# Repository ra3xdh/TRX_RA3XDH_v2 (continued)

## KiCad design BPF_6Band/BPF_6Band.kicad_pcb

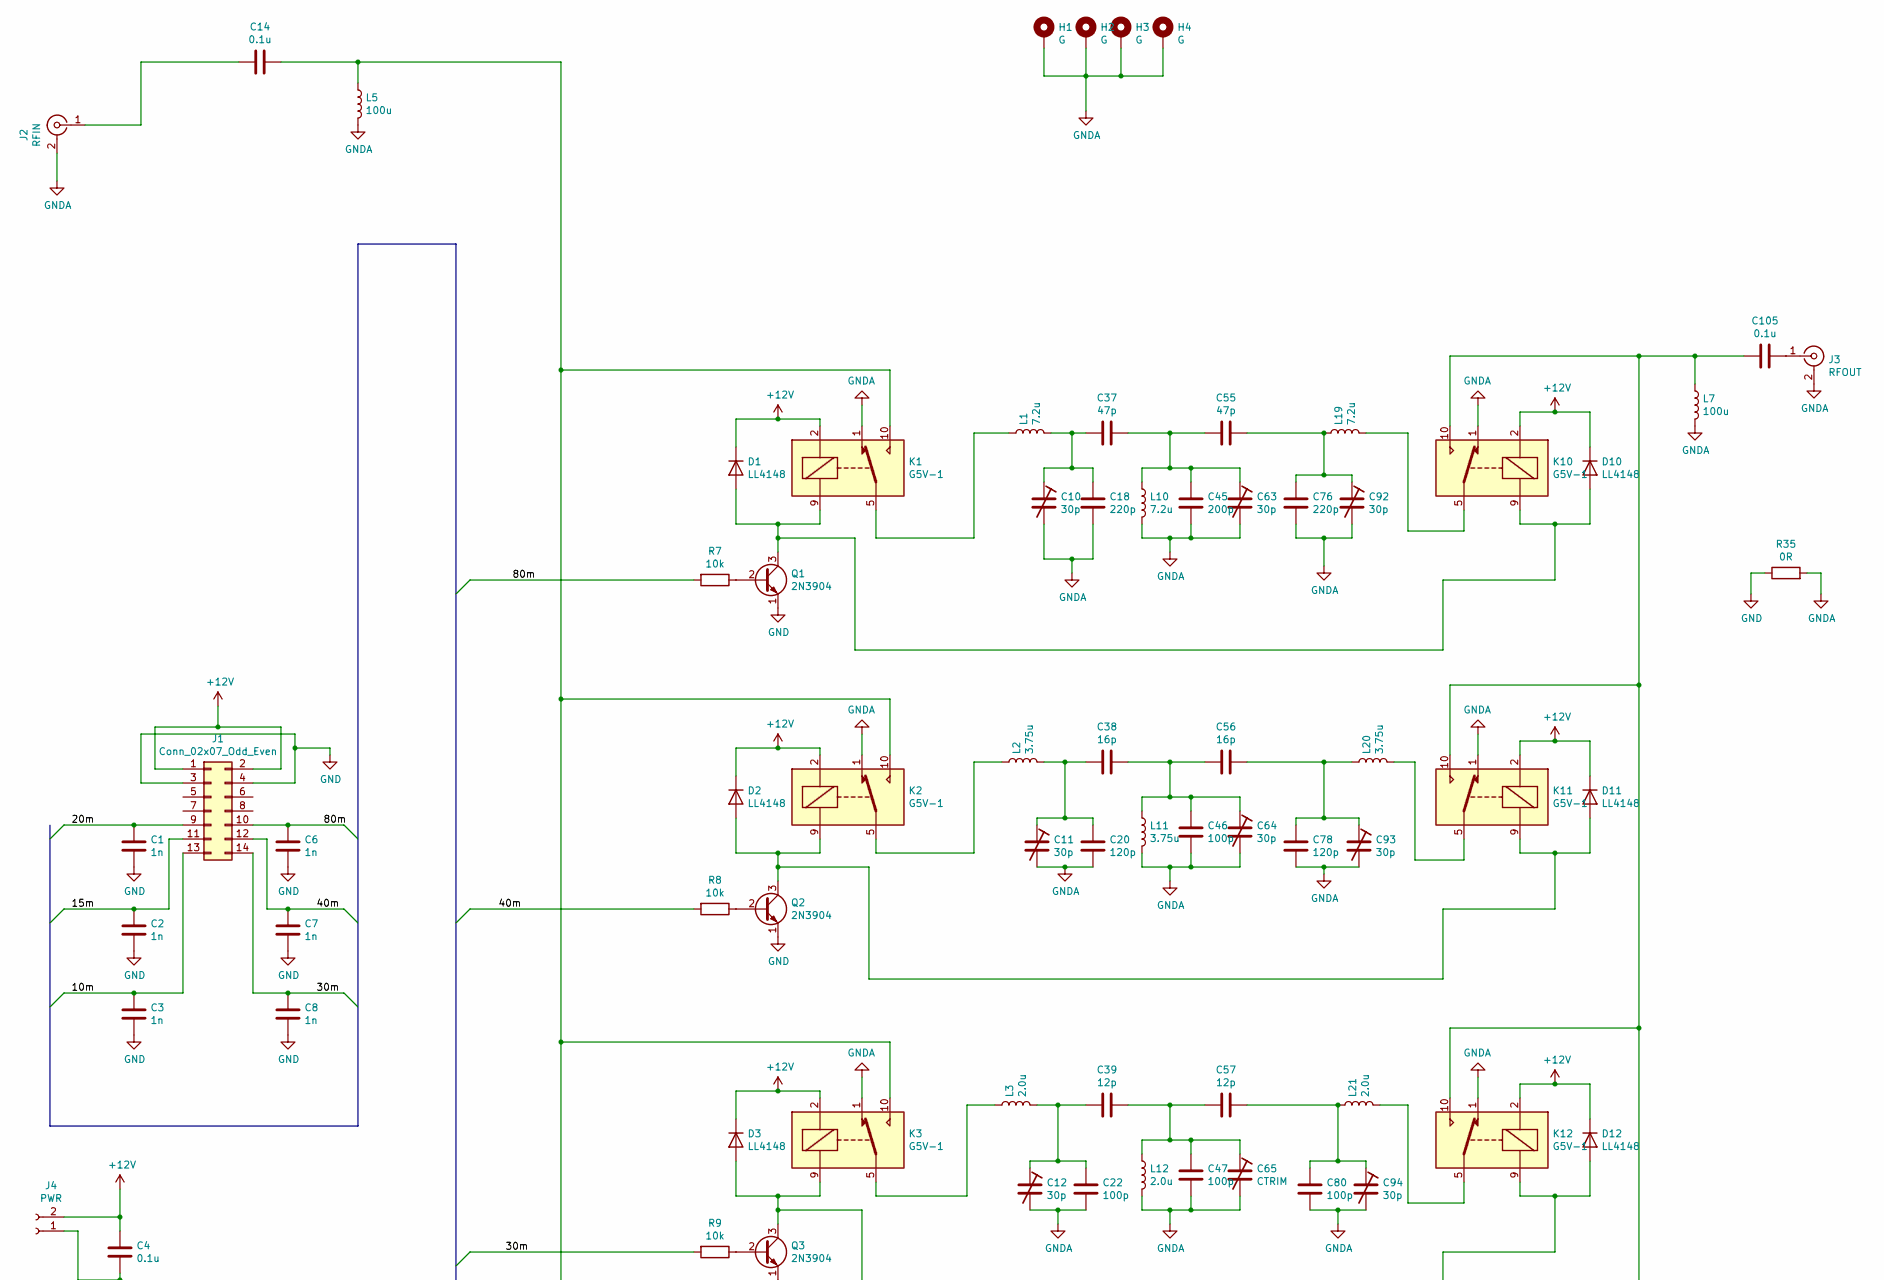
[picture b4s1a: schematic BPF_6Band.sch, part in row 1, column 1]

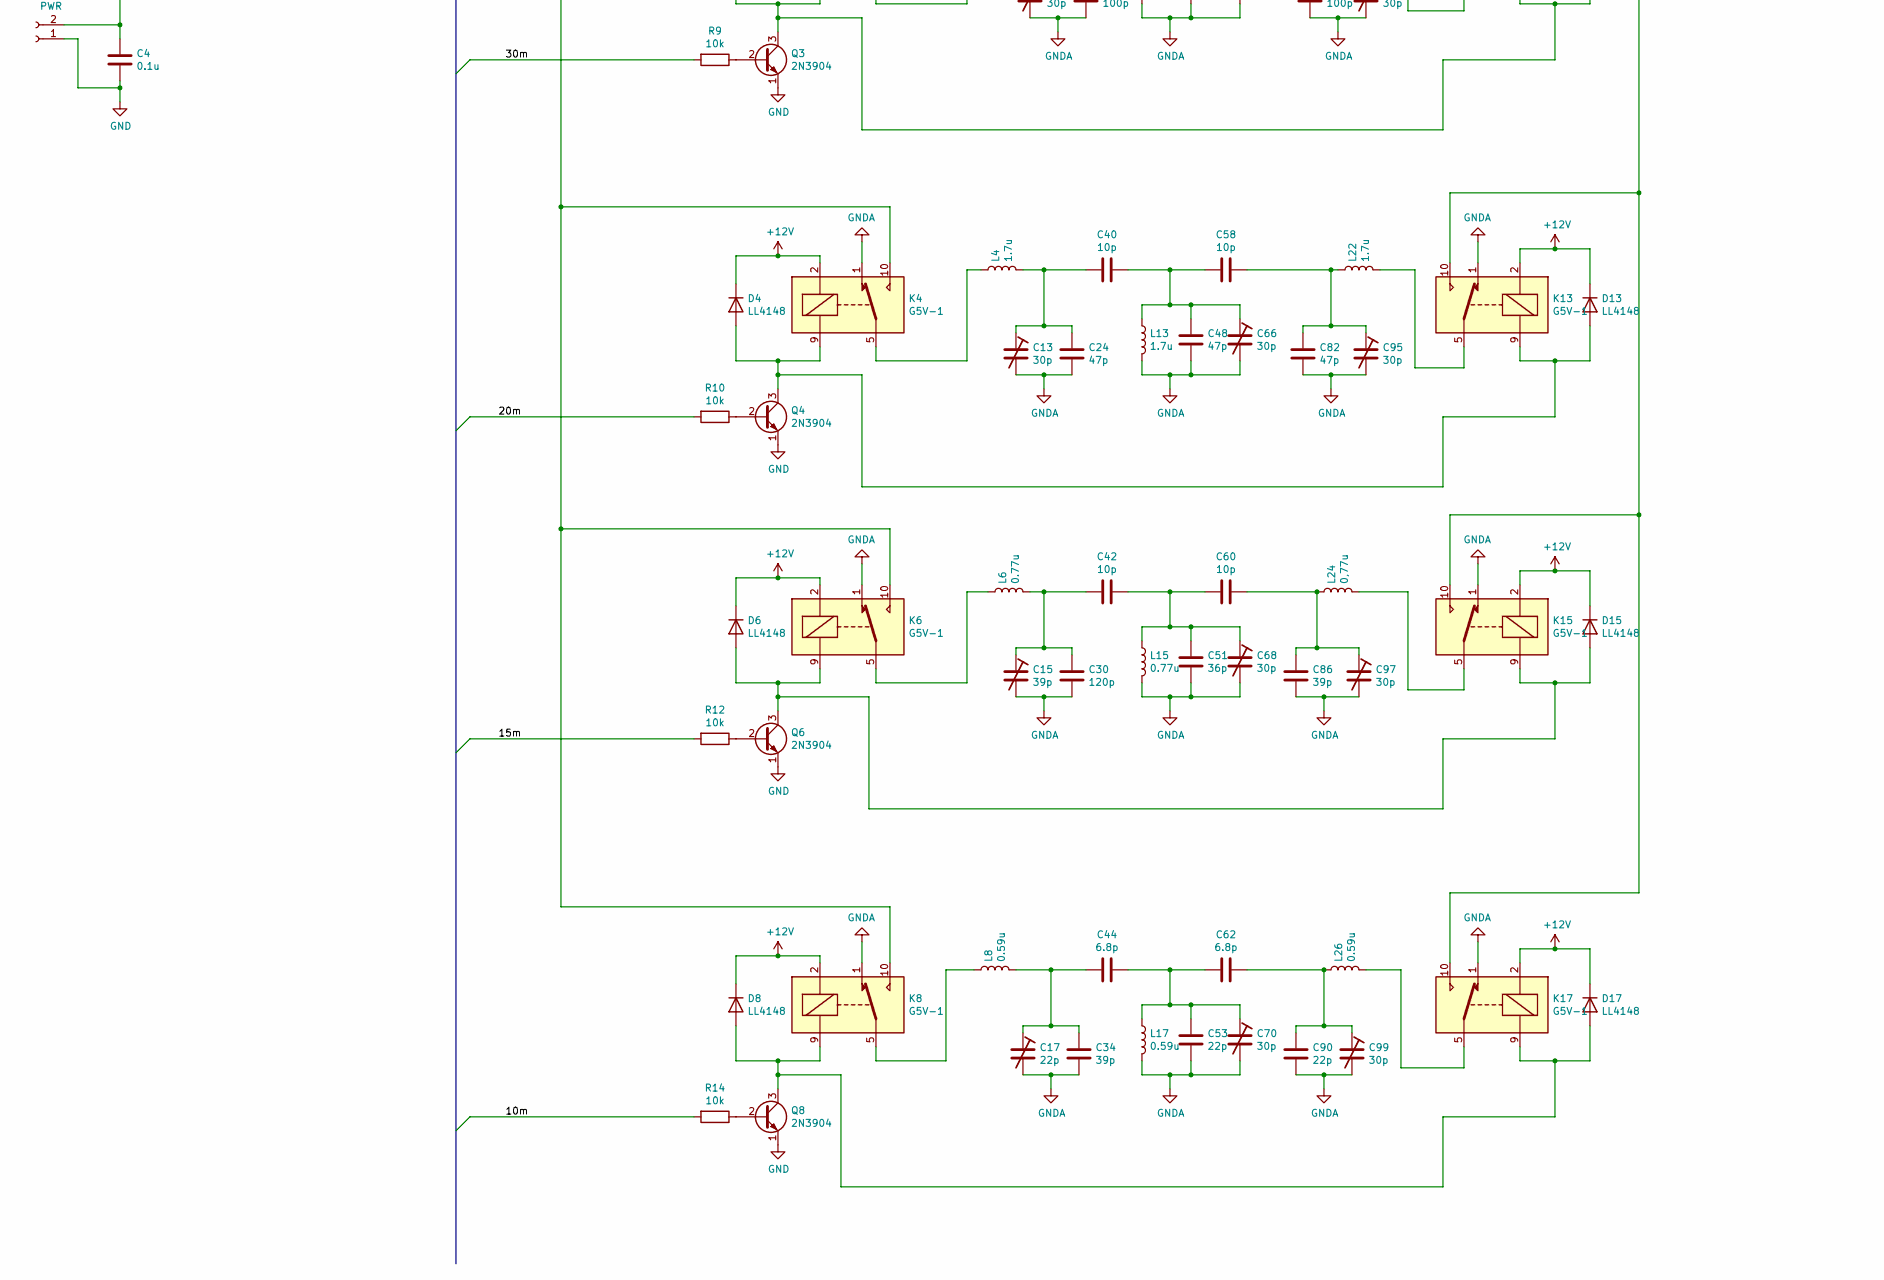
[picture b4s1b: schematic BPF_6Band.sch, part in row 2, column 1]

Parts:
C1, C2, C3, C6, C7, C8: 1n; C_0805_2012Metric
C4, C14, C105: 0.1u; C_0805_2012Metric
C10, C11, C12, C13, C63, C64, C66, C68, C70, C92, C93, C94, C95, C97, C99: 30p; Ctrimm_5mm
C15: 39p; Ctrimm_5mm
C17: 22p; Ctrimm_5mm
C18, C76: 220p; C_0805_2012Metric
C20, C30, C78: 120p; C_0805_2012Metric
C22, C46, C47, C80: 100p; C_0805_2012Metric
C24, C37, C48, C55, C82: 47p; C_0805_2012Metric
C34, C86: 39p; C_0805_2012Metric
C38, C56: 16p; C_0805_2012Metric
C39, C57: 12p; C_0805_2012Metric
C40, C42, C58, C60: 10p; C_0805_2012Metric
C44, C62: 6.8p; C_0805_2012Metric
C45: 200p; C_0805_2012Metric
C51: 36p; C_0805_2012Metric
C53, C90: 22p; C_0805_2012Metric
C65: CTRIM; Ctrimm_5mm
D1, D2, D3, D4, D6, D8, D10, D11, D12, D13, D15, D17: LL4148; D_MiniMELF
H1, H2, H3, H4: G; MountingHole_3.2mm_M3_ISO7380_Pad
J1: Conn_02x07_Odd_Even; IDC-Header_2x07_P2.54mm_Vertical
J2: RFIN; SMA_Amphenol_132291_Vertical
J3: RFOUT; SMA_Amphenol_132291_Vertical
J4: PWR; JST_EH_B2B-EH-A_1x02_P2.50mm_Vertical
K1, K2, K3, K4, K6, K8, K10, K11, K12, K13, K15, K17: G5V-1; Relay_SPDT_Omron_G5V-1
L1, L10, L19: 7.2u; L_Toroid_Vertical_L10.0mm_W5.0mm_P5.08mm
L2, L11, L20: 3.75u; L_Toroid_Vertical_L10.0mm_W5.0mm_P5.08mm
L3, L12, L21: 2.0u; L_Toroid_Vertical_L10.0mm_W5.0mm_P5.08mm
L4, L13, L22: 1.7u; L_Toroid_Vertical_L10.0mm_W5.0mm_P5.08mm
L5, L7: 100u; L_Radial_D8.7mm_P5.00mm_Fastron_07HCP
L6, L15: 0.77u; L_Toroid_Vertical_L10.0mm_W5.0mm_P5.08mm
L8, L17, L26: 0.59u; L_Toroid_Vertical_L10.0mm_W5.0mm_P5.08mm
L24: 0,77u; L_Toroid_Vertical_L10.0mm_W5.0mm_P5.08mm
Q1, Q2, Q3, Q4, Q6, Q8: 2N3904; TO-92_Inline
R7, R8, R9, R10, R12, R14: 10k; R_0805_2012Metric
R35: 0R; R_0805_2012Metric

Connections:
+12V: C4.1, D1.1 (K), D2.1 (K), D3.1 (K), D4.1 (K), D6.1 (K), D8.1 (K), D10.1 (K), D11.1 (K), D12.1 (K), D13.1 (K), D15.1 (K), D17.1 (K), J1.1, J1.2, J4.2, K1.2, K2.2, K3.2, K4.2, K6.2, K8.2, K10.2, K11.2, K12.2, K13.2, K15.2, K17.2
/10m: C3.1, J1.13, R14.2
/15m: C2.1, J1.11, R12.2
/20m: C1.1, J1.9, R10.2
/30m: C8.1, J1.14, R9.2
/40m: C7.1, J1.12, R8.2
/80m: C6.1, J1.10, R7.2
GND: C1.2, C2.2, C3.2, C4.2, C6.2, C7.2, C8.2, J1.3, J1.4, J4.1, Q1.1 (E), Q2.1 (E), Q3.1 (E), Q4.1 (E), Q6.1 (E), Q8.1 (E), R35.1
GNDA: C10.2, C11.2, C12.2, C13.2, C15.2, C17.2, C18.2, C20.2, C22.2, C24.2, C30.2, C34.2, C45.2, C46.2, C47.2, C48.2, C51.2, C53.2, C63.2, C64.2, C65.2, C66.2, C68.2, C70.2, C76.2, C78.2, C80.2, C82.2, C86.2, C90.2, C92.2, C93.2, C94.2, C95.2, C97.2, C99.2, H1.1, H2.1, H3.1, H4.1, J2.2 (Ext), J3.2 (Ext), K1.1, K2.1, K3.1, K4.1, K6.1, K8.1, K10.1, K11.1, K12.1, K13.1, K15.1, K17.1, L5.2, L7.2, L10.2, L11.2, L12.2, L13.2, L15.2, L17.2, R35.2
unnamed: C10.1, C18.1, C37.2, L1.2
unnamed: C11.1, C20.1, C38.2, L2.2
unnamed: C12.1, C22.1, C39.2, L3.2
unnamed: C13.1, C24.1, C40.2, L4.2
unnamed: C14.1, K1.10, K2.10, K3.10, K4.10, K6.10, K8.10, L5.1
unnamed: C14.2, J2.1 (In)
unnamed: C15.1, C30.1, C42.2, L6.2
unnamed: C17.1, C34.1, C44.2, L8.2
unnamed: C37.1, C45.1, C55.2, C63.1, L10.1
unnamed: C38.1, C46.1, C56.2, C64.1, L11.1
unnamed: C39.1, C47.1, C57.2, C65.1, L12.1
unnamed: C40.1, C48.1, C58.2, C66.1, L13.1
unnamed: C42.1, C51.1, C60.2, C68.1, L15.1
unnamed: C44.1, C53.1, C62.2, C70.1, L17.1
unnamed: C55.1, C76.1, C92.1, L19.1
unnamed: C56.1, C78.1, C93.1, L20.1
unnamed: C57.1, C80.1, C94.1, L21.1
unnamed: C58.1, C82.1, C95.1, L22.1
unnamed: C60.1, C86.1, C97.1, L24.1
unnamed: C62.1, C90.1, C99.1, L26.1
unnamed: C105.1, J3.1 (In)
unnamed: C105.2, K10.10, K11.10, K12.10, K13.10, K15.10, K17.10, L7.1
unnamed: D1.2 (A), D10.2 (A), K1.9, K10.9, Q1.3 (C)
unnamed: D2.2 (A), D11.2 (A), K2.9, K11.9, Q2.3 (C)
unnamed: D3.2 (A), D12.2 (A), K3.9, K12.9, Q3.3 (C)
unnamed: D4.2 (A), D13.2 (A), K4.9, K13.9, Q4.3 (C)
unnamed: D6.2 (A), D15.2 (A), K6.9, K15.9, Q6.3 (C)
unnamed: D8.2 (A), D17.2 (A), K8.9, K17.9, Q8.3 (C)
unnamed: K1.5, K1.6, L1.1
unnamed: K2.5, K2.6, L2.1
unnamed: K3.5, K3.6, L3.1
unnamed: K4.5, K4.6, L4.1
unnamed: K6.5, K6.6, L6.1
unnamed: K8.5, K8.6, L8.1
unnamed: K10.5, K10.6, L19.2
unnamed: K11.5, K11.6, L20.2
unnamed: K12.5, K12.6, L21.2
unnamed: K13.5, K13.6, L22.2
unnamed: K15.5, K15.6, L24.2
unnamed: K17.5, K17.6, L26.2
unnamed: Q1.2 (B), R7.1
unnamed: Q2.2 (B), R8.1
unnamed: Q3.2 (B), R9.1
unnamed: Q4.2 (B), R10.1
unnamed: Q6.2 (B), R12.1
unnamed: Q8.2 (B), R14.1

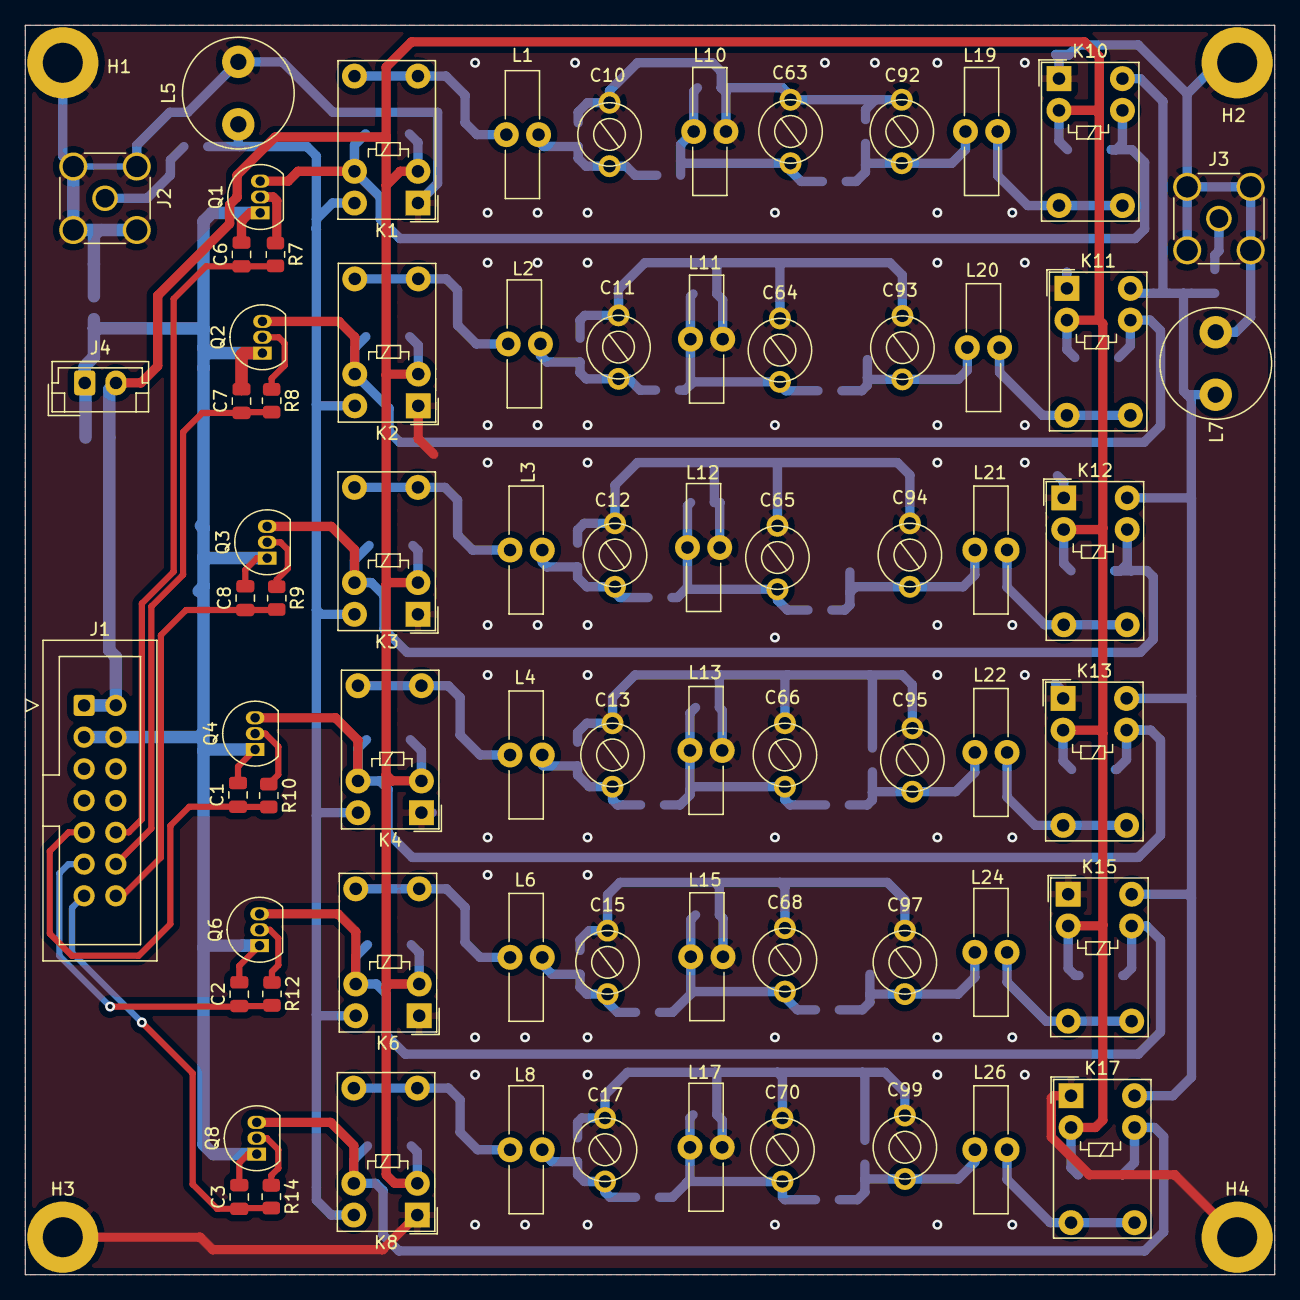
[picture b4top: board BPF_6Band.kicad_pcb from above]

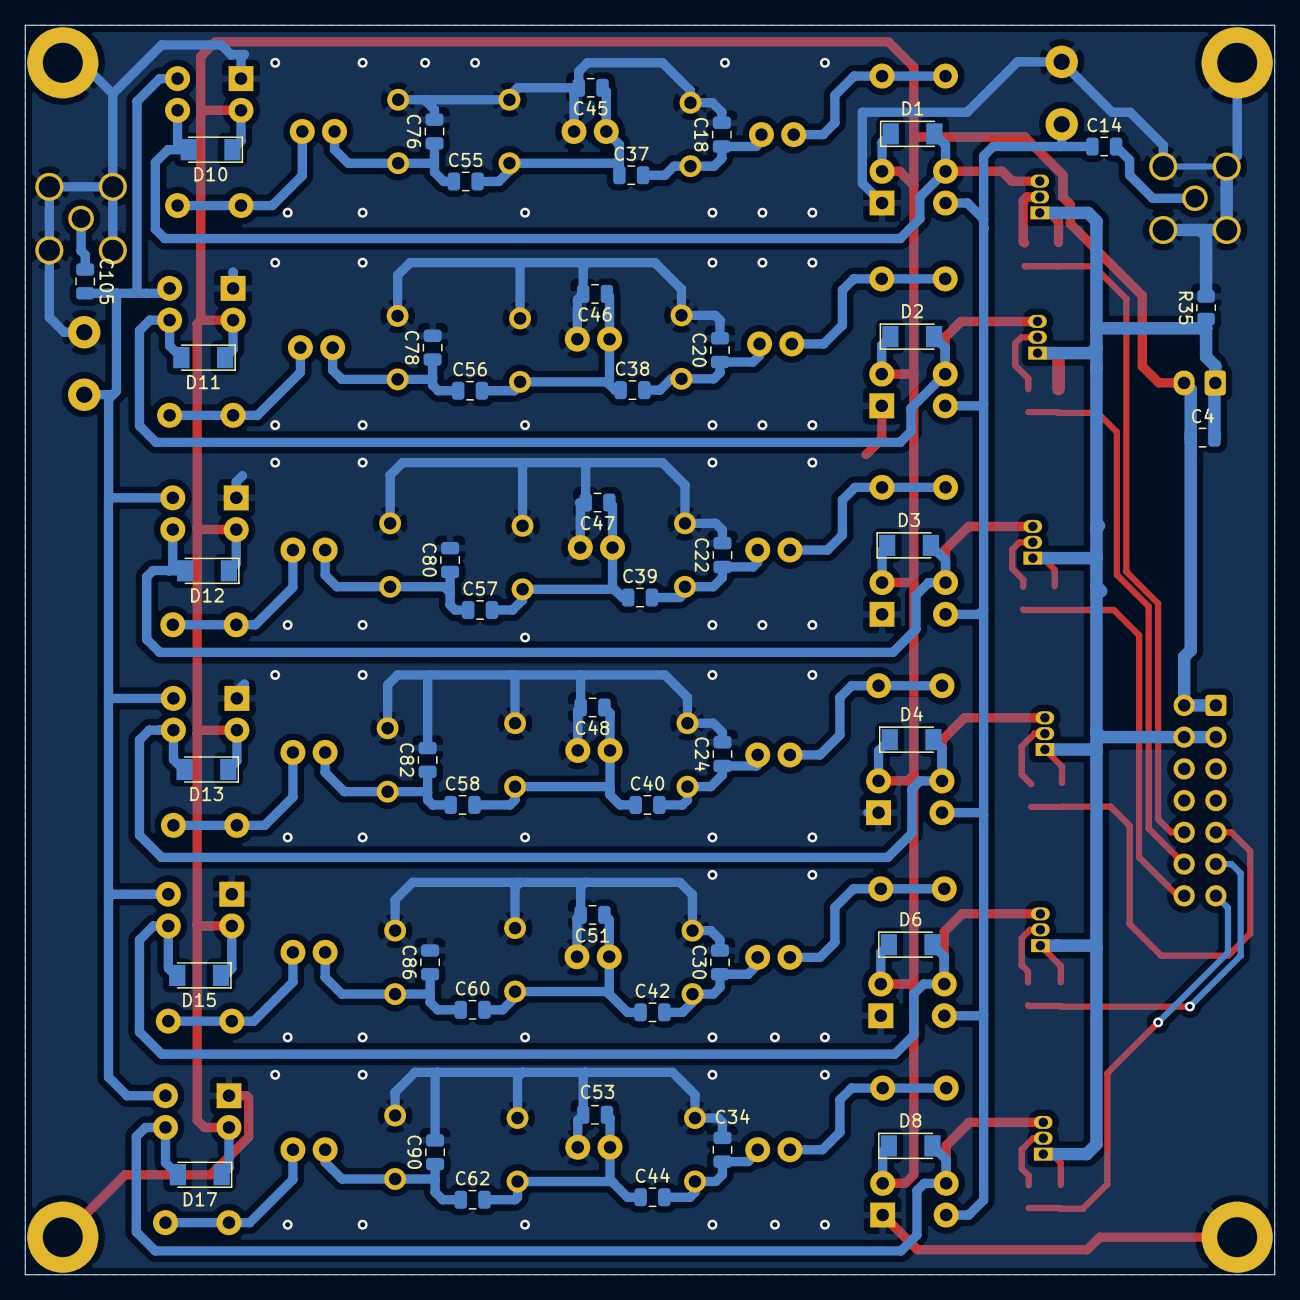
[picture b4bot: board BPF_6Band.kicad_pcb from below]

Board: 2 copper layers, 100.0 x 100.0 mm, 122 parts (46 on the bottom side), 55 nets.

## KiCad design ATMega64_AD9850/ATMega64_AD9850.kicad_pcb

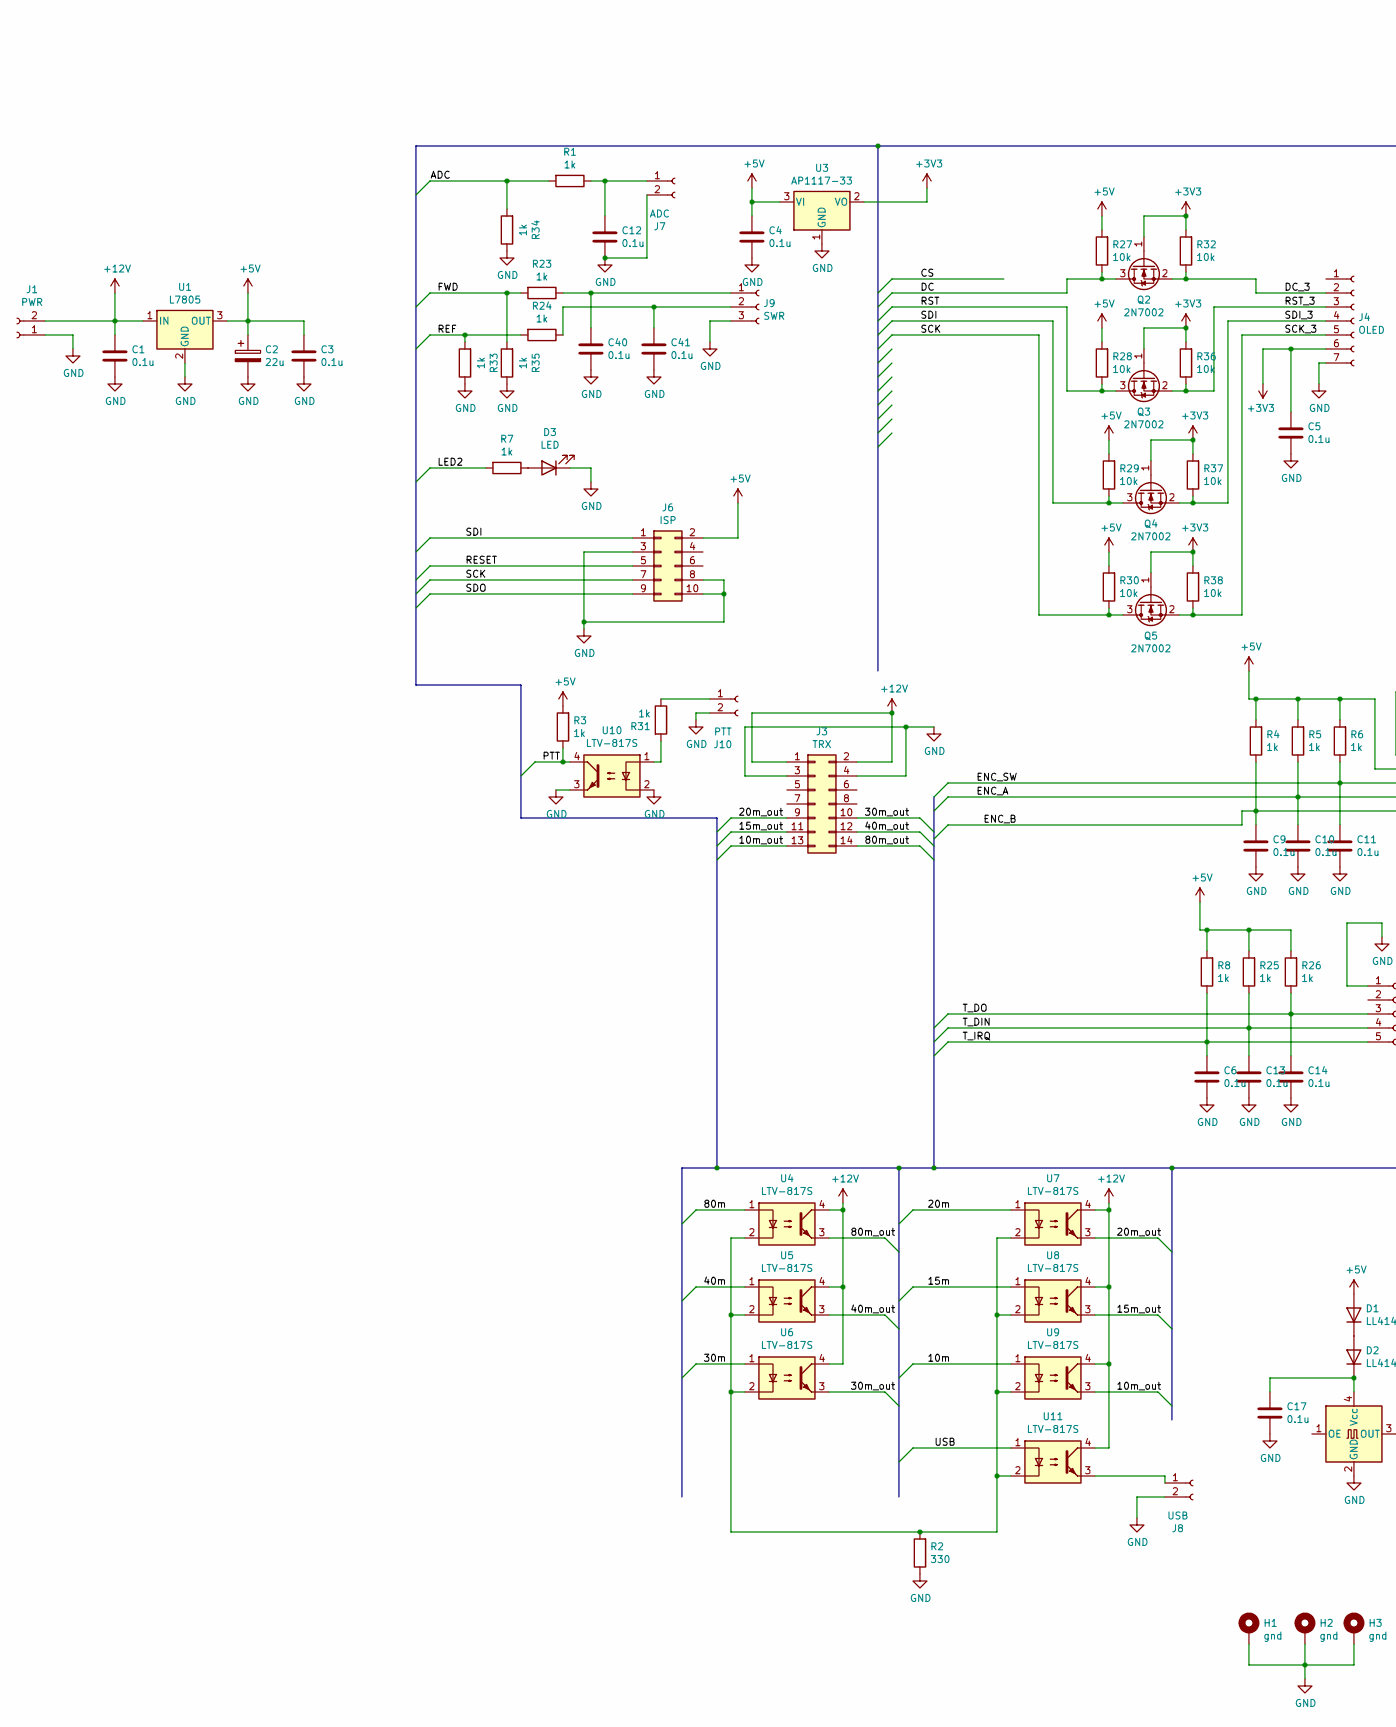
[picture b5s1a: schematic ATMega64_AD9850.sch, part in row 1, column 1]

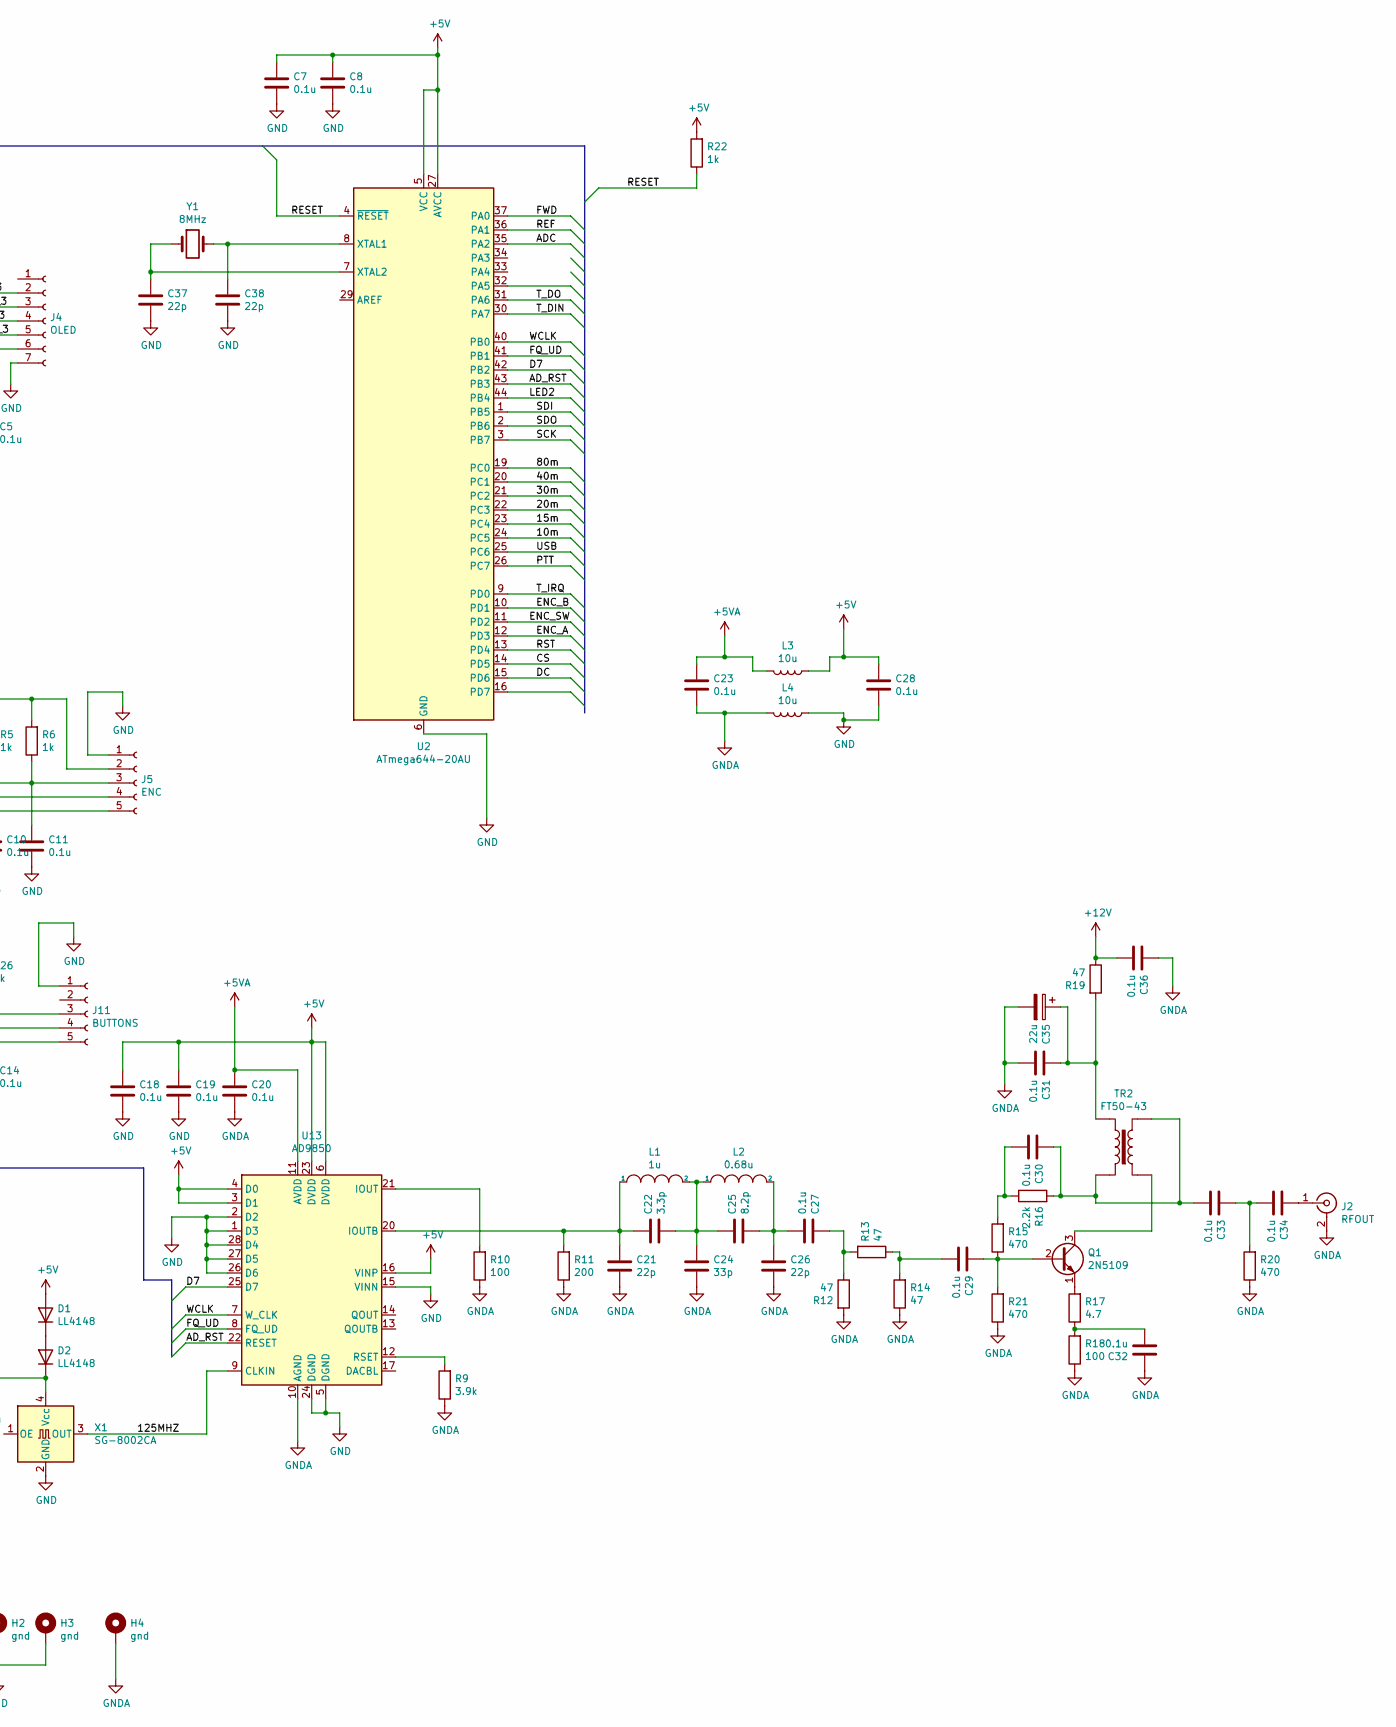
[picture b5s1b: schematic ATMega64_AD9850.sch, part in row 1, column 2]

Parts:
C1, C3, C4, C5, C6, C7, C8, C9, C10, C11, C12, C13, C14, C17, C18, C19, C20, C23, C27, C28, C29, C30, C31, C32, C33, C34, C36, C40, C41: 0.1u; C_0805_2012Metric
C2, C35: 22u; CP_Radial_D5.0mm_P2.50mm
C21, C26, C37, C38: 22p; C_0805_2012Metric
C22: 3.3p; C_0805_2012Metric
C24: 33p; C_0805_2012Metric
C25: 8.2p; C_0805_2012Metric
D1, D2: LL4148; D_MiniMELF
D3: LED; LED_D3.0mm
H1, H2, H3, H4: gnd; MountingHole_3.2mm_M3_DIN965_Pad
J1: PWR; JST_EH_B2B-EH-A_1x02_P2.50mm_Vertical
J2: RFOUT; SMA_Amphenol_132291_Vertical
J3: TRX; IDC-Header_2x07_P2.54mm_Vertical
J4: OLED; PinHeader_1x07_P2.54mm_Vertical
J5: ENC; JST_EH_B5B-EH-A_1x05_P2.50mm_Vertical
J6: ISP; IDC-Header_2x05_P2.54mm_Vertical
J7: ADC; JST_EH_B2B-EH-A_1x02_P2.50mm_Vertical
J8: USB; JST_EH_B2B-EH-A_1x02_P2.50mm_Vertical
J9: SWR; JST_EH_B3B-EH-A_1x03_P2.50mm_Vertical
J10: PTT; JST_EH_B2B-EH-A_1x02_P2.50mm_Vertical
J11: BUTTONS; JST_EH_B5B-EH-A_1x05_P2.50mm_Vertical
L1: 1u; L_Toroid_Vertical_L10.0mm_W5.0mm_P5.08mm
L2: 0.68u; L_Toroid_Vertical_L10.0mm_W5.0mm_P5.08mm
L3, L4: 10u; L_Axial_L11.0mm_D4.5mm_P15.24mm_Horizontal_Fastron_MECC
Q1: 2N5109; TO-39-3
Q2, Q3, Q4, Q5: 2N7002; SOT-23
R1, R3, R4, R5, R6, R7, R8, R22, R23, R24, R25, R26, R31, R33, R34, R35: 1k; R_0805_2012Metric
R2: 330; R_0805_2012Metric
R9: 3.9k; R_0805_2012Metric
R10, R18: 100; R_0805_2012Metric
R11: 200; R_0805_2012Metric
R12, R13, R14, R19: 47; R_0805_2012Metric
R15, R20, R21: 470; R_0805_2012Metric
R16: 2.2k; R_0805_2012Metric
R17: 4.7; R_0805_2012Metric
R27, R28, R29, R30, R32, R36, R37, R38: 10k; R_0805_2012Metric
TR2: FT50-43; L_Toroid_Vertical_L10.0mm_W5.0mm_4pin
U1: L7805; TO-220-3_Vertical
U2: ATmega644-20AU; TQFP-44_10x10mm_P0.8mm
U3: AP1117-33; SOT-223-3_TabPin2
U4, U5, U6, U7, U8, U9, U10, U11: LTV-817S; SMDIP-4_W9.53mm
U13: AD9850; SSOP-28_5.3x10.2mm_P0.65mm
X1: SG-8002CA; Oscillator_SMD_SeikoEpson_SG8002CA-4Pin_7.0x5.0mm
Y1: 8MHz; Crystal_HC49-U_Vertical

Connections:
+3V3: C5.1, J4.6, Q2.1 (G), Q3.1 (G), Q4.1 (G), Q5.1 (G), R32.2, R36.2, R37.2, R38.2, U3.2 (VO)
+5V: C2.1, C3.1, C4.1, C7.1, C8.1, C18.1, C19.1, C28.1, D1.2 (A), J5.2, J6.2, L3.1, R3.2, R4.2, R5.2, R6.2, R8.2, R22.2, R25.2, R26.2, R27.2, R28.2, R29.2, R30.2, U1.3 (OUT), U2.5 (VCC), U2.17 (VCC), U2.27 (AVCC), U2.38 (VCC), U3.3 (VI), U13.3 (D1), U13.4 (D0), U13.6 (DVDD), U13.16 (VINP), U13.23 (DVDD)
+5VA: C20.1, C23.1, L3.2, U13.11 (AVDD), U13.18 (AVDD)
+12V: C1.1, C36.2, J1.2, J3.1, J3.2, R19.1, U1.1 (IN), U4.4, U5.4, U6.4, U7.4, U8.4, U9.4, U11.4
/10m: U2.24 (PC5), U9.1
/10m_out: J3.13, U9.3
/15m: U2.23 (PC4), U8.1
/15m_out: J3.11, U8.3
/20m: U2.22 (PC3), U7.1
/20m_out: J3.9, U7.3
/30m: U2.21 (PC2), U6.1
/30m_out: J3.10, U6.3
/40m: U2.20 (PC1), U5.1
/40m_out: J3.12, U5.3
/80m: U2.19 (PC0), U4.1
/80m_out: J3.14, U4.3
/125MHZ: U13.9 (CLKIN), X1.3 (OUT)
/ADC: R1.2, R34.2, U2.35 (PA2)
/AD_RST: U2.43 (PB3), U13.22 (RESET)
/D7: U2.42 (PB2), U13.25 (D7)
/DC: Q2.3 (D), R27.1, U2.15 (PD6)
/DC_3: J4.2, Q2.2 (S), R32.1
/ENC_A: C10.1, J5.4, R5.1, U2.12 (PD3)
/ENC_B: C9.1, J5.5, R4.1, U2.10 (PD1)
/ENC_SW: C11.1, J5.3, R6.1, U2.11 (PD2)
/FQ_UD: U2.41 (PB1), U13.8 (FQ_UD)
/FWD: R23.2, R35.2, U2.37 (PA0)
/LED2: R7.2, U2.44 (PB4)
/PTT: R3.1, U2.26 (PC7), U10.4
/REF: R24.2, R33.2, U2.36 (PA1)
/RESET: J6.5, R22.1, U2.4 (~RESET)
/RST: Q3.3 (D), R28.1, U2.13 (PD4)
/RST_3: J4.3, Q3.2 (S), R36.1
/SCK: J6.7, Q5.3 (D), R30.1, U2.3 (PB7)
/SCK_3: J4.5, Q5.2 (S), R38.1
/SDI: J6.1, Q4.3 (D), R29.1, U2.1 (PB5)
/SDI_3: J4.4, Q4.2 (S), R37.1
/SDO: J6.9, U2.2 (PB6)
/T_DIN: C13.1, J11.4, R25.1, U2.30 (PA7)
/T_DO: C14.1, J11.3, R26.1, U2.31 (PA6)
/T_IRQ: C6.1, J11.5, R8.1, U2.9 (PD0)
/USB: U2.25 (PC6), U11.1
/WCLK: U2.40 (PB0), U13.7 (W_CLK)
GND: C1.2, C2.2, C3.2, C4.2, C5.2, C6.2, C7.2, C8.2, C9.2, C10.2, C11.2, C12.2, C13.2, C14.2, C17.2, C18.2, C19.2, C28.2, C37.2, C38.2, C40.2, C41.2, D3.1 (K), H1.1, H2.1, H3.1, J1.1, J3.3, J3.4, J4.7, J5.1, J6.3, J6.8, J6.10, J7.2, J8.2, J9.3, J10.2, J11.1, L4.1, R2.1, R33.1, R34.1, R35.1, U1.2 (GND), U2.6 (GND), U2.18 (GND), U2.28 (GND), U2.39 (GND), U3.1 (GND), U10.2, U10.3, U13.1 (D3), U13.2 (D2), U13.5 (DGND), U13.15 (VINN), U13.24 (DGND), U13.26 (D6), U13.27 (D5), U13.28 (D4), X1.2 (GND)
GNDA: C20.2, C21.2, C23.2, C24.2, C26.2, C31.2, C32.1, C35.2, C36.1, H4.1, J2.2 (Ext), L4.2, R9.1, R10.1, R11.1, R12.2, R14.1, R18.1, R20.1, R21.1, U13.10 (AGND), U13.19 (AGND)
unnamed: C12.1, J7.1, R1.1
unnamed: C17.1, D2.1 (K), X1.4 (Vcc)
unnamed: C21.1, C22.1, L1.1, R11.2, U13.20 (IOUTB)
unnamed: C22.2, C24.1, C25.1, L1.2, L2.1
unnamed: C25.2, C26.1, C27.2, L2.2
unnamed: C27.1, R12.1, R13.2
unnamed: C29.1, Q1.2 (B), R15.1, R21.2
unnamed: C29.2, R13.1, R14.2
unnamed: C30.1, C33.2, R16.2, TR2.2, TR2.4
unnamed: C30.2, R15.2, R16.1
unnamed: C31.1, C35.1, R19.2, TR2.3
unnamed: C32.2, R17.1, R18.2
unnamed: C33.1, C34.2, R20.2
unnamed: C34.1, J2.1 (In)
unnamed: C37.1, U2.7 (XTAL2), Y1.1
unnamed: C38.1, U2.8 (XTAL1), Y1.2
unnamed: C40.1, J9.1, R23.1
unnamed: C41.1, J9.2, R24.1
unnamed: D1.1 (K), D2.2 (A)
unnamed: D3.2 (A), R7.1
unnamed: J8.1, U11.3
unnamed: J10.1, R31.1
unnamed: Q1.1 (E), R17.2
unnamed: Q1.3 (C), TR2.1
unnamed: R2.2, U4.2, U5.2, U6.2, U7.2, U8.2, U9.2, U11.2
unnamed: R9.2, U13.12 (RSET)
unnamed: R10.2, U13.21 (IOUT)
unnamed: R31.2, U10.1

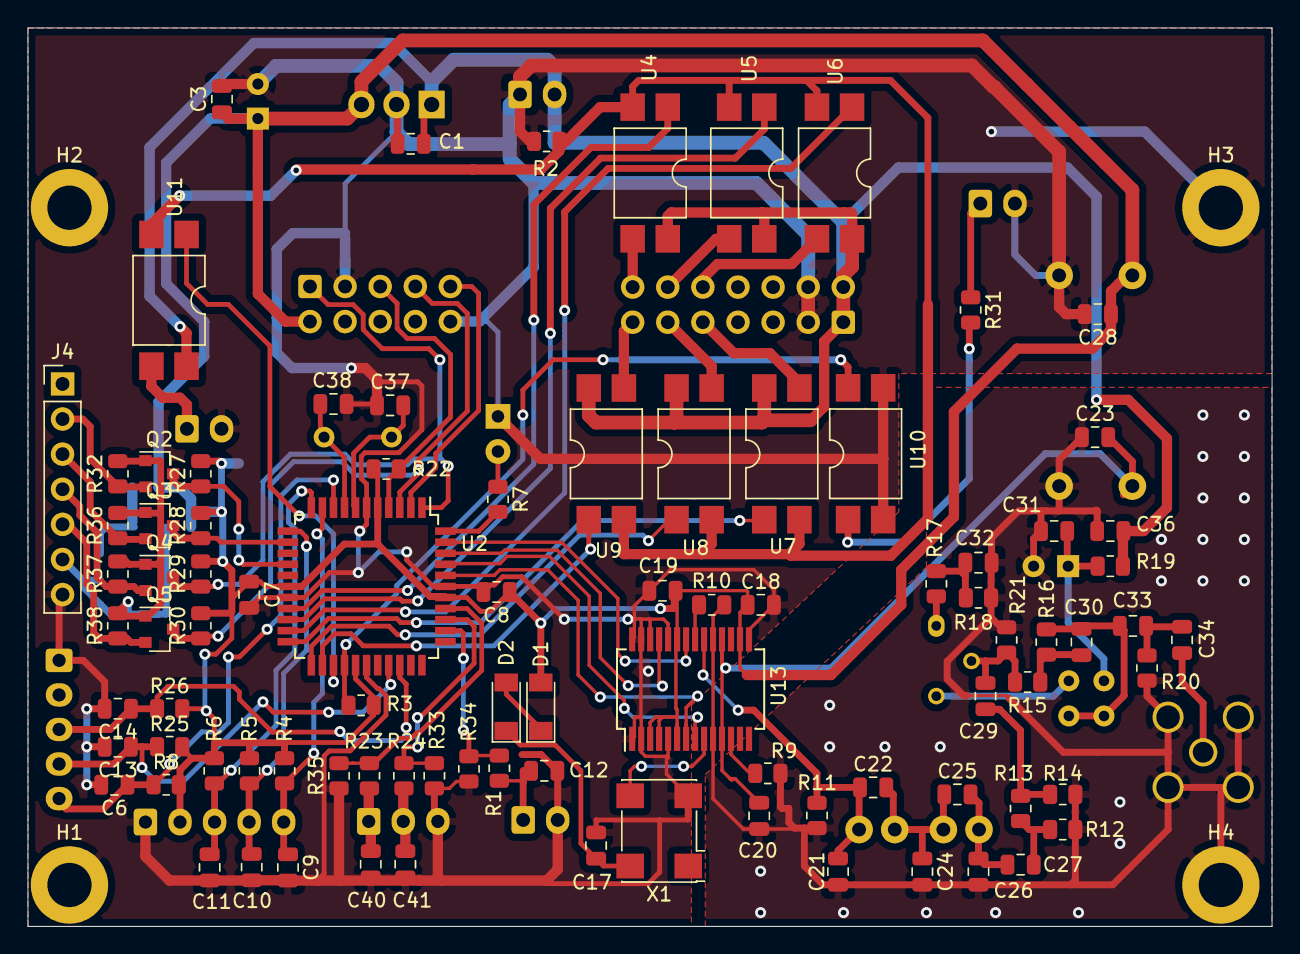
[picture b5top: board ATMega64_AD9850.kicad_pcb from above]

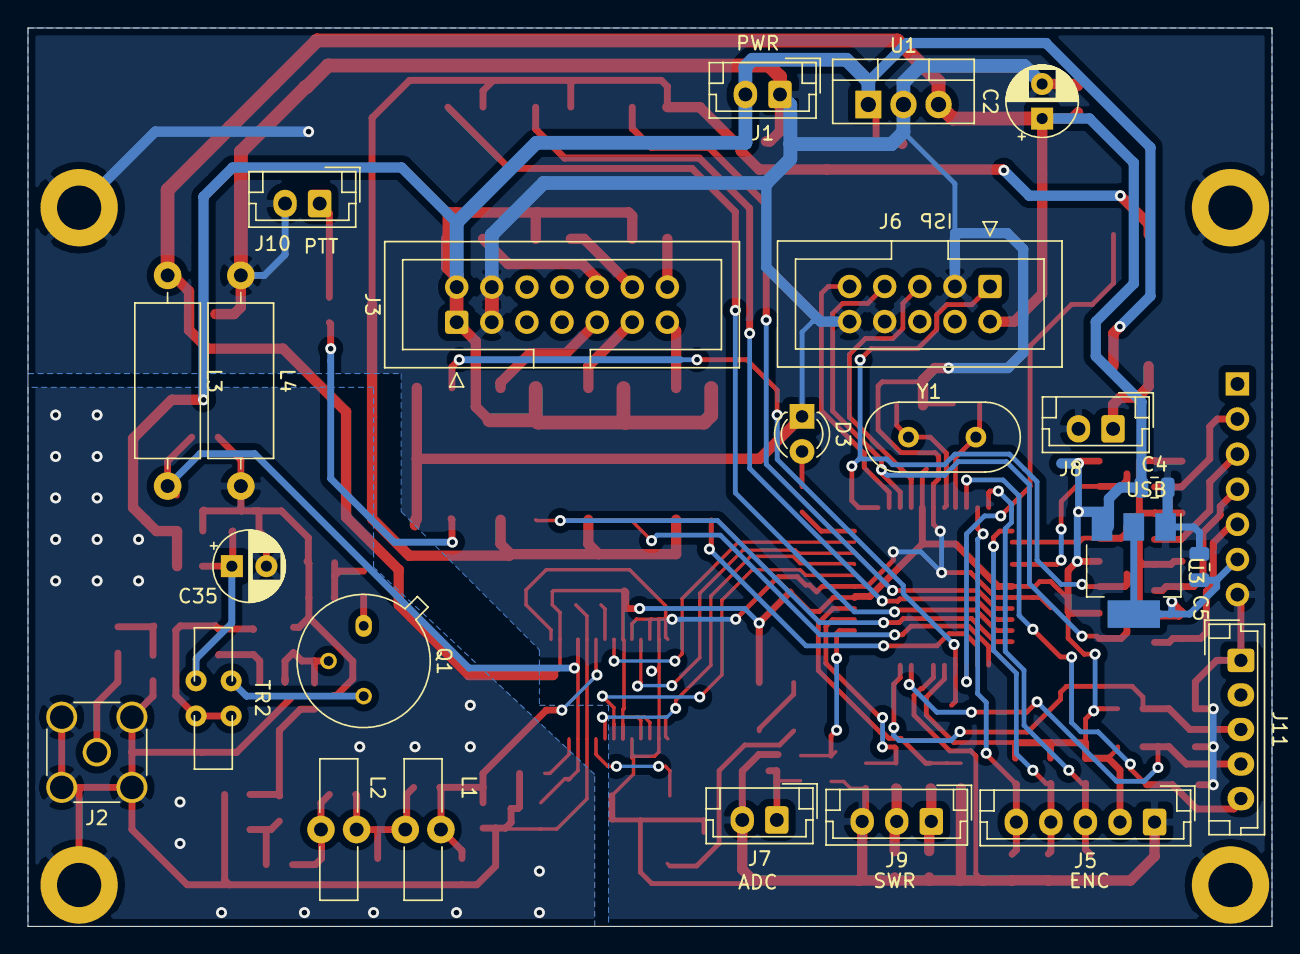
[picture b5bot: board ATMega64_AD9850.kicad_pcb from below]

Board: 2 copper layers, 90.0 x 65.0 mm, 118 parts (24 on the bottom side), 73 nets.

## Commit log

2021-11-29 Mainboard is opearational, assembled and tested
2021-11-29 Add readme
2021-11-29 Added AD9850 syntesizer
2021-12-04 Fixed BFO schematic
2021-12-04 Add 6-Band band N7DDC pass filter
2021-12-04 Added PA bypass and RF preamp boards
2021-12-04 Add PNG schematics
